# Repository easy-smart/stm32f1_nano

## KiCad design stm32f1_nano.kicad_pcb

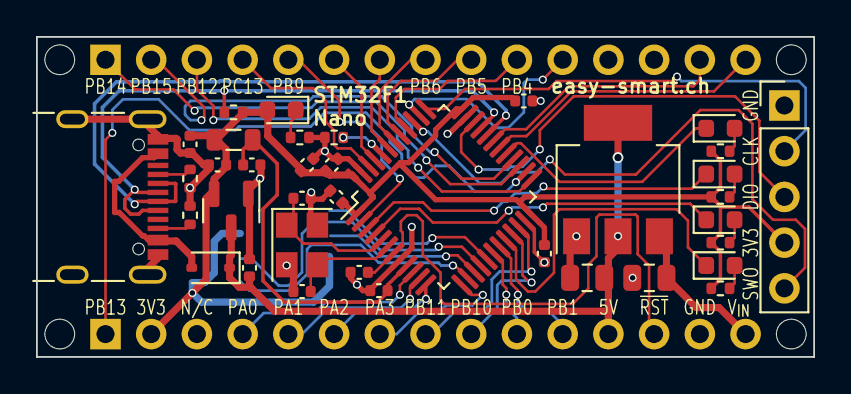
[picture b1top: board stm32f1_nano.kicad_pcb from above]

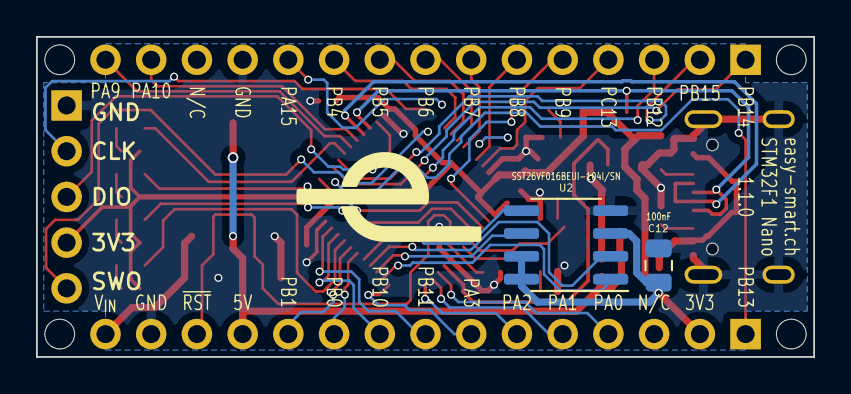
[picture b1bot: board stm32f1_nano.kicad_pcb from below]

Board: 2 copper layers, 43.2 x 17.8 mm, 45 parts (4 on the bottom side), 52 nets.

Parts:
C1, C6: 10n 50V; C_0402_1005Metric
C2, C3, C4, C5, C9: 100n 16V; C_0402_1005Metric
C7, C8, C17, C18: 1u 25V; C_0402_1005Metric
C10, C19: 20p 50V; C_0402_1005Metric
C12: 100nF; C_0805_2012Metric
C15, C16: 22u 25V; C_0805_2012Metric
D1: LED green; LED_0603_1608Metric
D2: LED yellow; LED_0603_1608Metric
D3: LED red; LED_0603_1608Metric
D4: LED blue; LED_0603_1608Metric
D8: PWR LED (grn); LED_0603_1608Metric
D9: 1N5819WS; D_SOD-323
J1: Analog; PinHeader_1x15_P2.54mm_Vertical
J2: Digital; PinHeader_1x15_P2.54mm_Vertical
J3: TYPE-C-31-M-12; SHOU HAN TYPE-C 16PIN 2MD(073)
J5: DEBUG; PinHeader_1x05_P2.54mm_Vertical
L1: 600Ω@100MHz; L_0805_2012Metric
MH1, MH2, MH3, MH4: MountingHole_65mil
R1, R11: 200; R_0402_1005Metric
R2, R3: 330; R_0402_1005Metric
R4: 150; R_0402_1005Metric
R5: 10k; R_0402_1005Metric
R6, R7: 5k1; R_0402_1005Metric
R8: 1k5; R_0402_1005Metric
U1: STM32F103C8T6; LQFP-48_7x7mm_P0.5mm
U2: SST26VF016BEUI-104I/SN; SOIC-8_3.9x4.9mm_P1.27mm
U4: XC6206P332MR; SOT-23
U5: AMS1117-5.0; SOT-223-3_TabPin2
Y1: X322516MLB4SI; Crystal_SMD_3225-4Pin_3.2x2.5mm

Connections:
+3.3V: C1.1, C2.1, C3.1, C4.1, C5.1, C8.1, C12.2, C18.1, D8.2 (A), J1.2, J5.4, L1.2, R2.2, R3.2, R4.2, R8.1, R11.2, U1.1 (VBAT), U1.24 (VDD), U1.36 (VDD), U1.48 (VDD), U2.3 (~WP), U2.7 (~HOLD), U2.8 (VDD), U4.2 (VO)
+3.3VA: C6.1, C7.1, L1.1, U1.9 (VDDA)
+5V: C16.1, C17.1, D9.1 (K), J1.12, U4.3 (VI), U5.2 (VO)
+12V: C15.1, J1.15, U5.3 (VI)
/BOOT0: R5.1, U1.44 (BOOT0)
/HSE_IN: C19.2, U1.5 (PD0), Y1.1
/HSE_OUT: C10.2, U1.6 (PD1), Y1.3
/LED1_GRN: D1.1 (K), U1.4 (PC15)
/LED2_ORG: D2.1 (K), U1.3 (PC14)
/LED3_RED: D3.1 (K), U1.29 (PA8)
/LED4_BLU: D4.1 (K), U1.20 (PB2)
/PA0: J1.4, U1.10 (PA0)
/PA1: J1.5, U1.11 (PA1)
/PA2: J1.6, U1.12 (PA2)
/PA3: J1.7, U1.13 (PA3)
/PA9: J2.15, U1.30 (PA9)
/PA10: J2.14, U1.31 (PA10)
/PA15: J2.11, U1.38 (PA15)
/PB0: J1.10, U1.18 (PB0)
/PB1: J1.11, U1.19 (PB1)
/PB4: J2.10, U1.40 (PB4)
/PB5: J2.9, U1.41 (PB5)
/PB6: J2.8, U1.42 (PB6)
/PB7: J2.7, U1.43 (PB7)
/PB8: J2.6, U1.45 (PB8)
/PB9: J2.4, U1.46 (PB9)
/PB10: J1.9, U1.21 (PB10)
/PB11: J1.8, U1.22 (PB11)
/PB12: J2.3, U1.25 (PB12)
/PB13: J1.1, U1.26 (PB13)
/PB14: J2.1, U1.27 (PB14)
/PB15: J2.2, U1.28 (PB15)
/PC13: J2.5, U1.2 (PC13)
/SPI1_MISO: U1.16 (PA6), U2.2 (SO)
/SPI1_MOSI: U1.17 (PA7), U2.5 (SI)
/SPI1_NSS: U1.14 (PA4), U2.1 (~CE)
/SPI1_SCK: U1.15 (PA5), U2.6 (SCK)
/USB_D+: J3.A6 (D+), J3.B6 (D+), R8.2, U1.33 (PA12)
/USB_D-: J3.A7 (D-), J3.B7 (D-), U1.32 (PA11)
/~RESET: C9.1, J1.13, U1.7 (NRST)
GND: C1.2, C2.2, C3.2, C4.2, C5.2, C6.2, C7.2, C8.2, C9.2, C10.1, C12.1, C15.2, C16.2, C17.2, C18.2, C19.1, J1.14, J2.12, J3.A1 (GND), J3.A12 (GND), J3.B1 (GND), J3.B12 (GND), J3.S1 (SHIELD), J5.1, R1.1, R5.2, R6.1, R7.1, U1.8 (VSSA), U1.23 (VSS), U1.35 (VSS), U1.47 (VSS), U2.4 (VSS), U4.1 (GND), U5.1 (GND), Y1.2, Y1.4
unnamed: D1.2 (A), R11.1
unnamed: D2.2 (A), R2.1
unnamed: D3.2 (A), R3.1
unnamed: D4.2 (A), R4.1
unnamed: D8.1 (K), R1.2
unnamed: J3.A5 (CC1), R6.2
unnamed: J3.B5 (CC2), R7.2
SWCLK: J5.2, U1.37 (PA14)
SWDIO: J5.3, U1.34 (PA13)
SWO: J5.5, U1.39 (PB3)
VBUS: D9.2 (A), J3.A4 (VBUS), J3.A9 (VBUS), J3.B4 (VBUS), J3.B9 (VBUS)

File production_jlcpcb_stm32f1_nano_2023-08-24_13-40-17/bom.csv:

Designator,Footprint,Quantity,Value,LCSC Part #
"C1, C6",0402,2,10n 50V,C15195
"C10, C19",0402,2,20p 50V,C1554
"C15, C16",0805,2,22u 25V,C45783
"C17, C18, C7, C8",0402,4,1u 25V,C52923
"C2, C3, C4, C5, C9",0402,5,100n 16V,C1525
D1,0603,1,LED green,C72043
D2,0603,1,LED yellow,C72038
D3,0603,1,LED red,C2286
D4,0603,1,LED blue,C72041
D8,0603,1,LED red (PWR),C2286
D9,D_SOD-323,1,1N5819WS,C191023
J3,USB_C_Receptacle_HRO_TYPE-C-31-M-12,1,TYPE-C-31-M-12,C165948
L1,0805,1,600Ω@100MHz,C1017
"R1, R2, R3",0402,3,300,C25102
"R11, R4",0402,2,75,C25133
R5,0402,1,10k,C25744
"R6, R7",0402,2,5k1,C25905
R8,0402,1,1k5,C25867
U1,LQFP-48_7x7mm_P0.5mm,1,STM32F103C8T6,C8734
U4,SOT-23-3,1,XC6206P332MR,C5446
U5,SOT-223-3_TabPin2,1,AMS1117-5.0,DNP
Y1,Crystal_SMD_3225-4Pin_3.2x2.5mm,1,X322516MLB4SI,C13738

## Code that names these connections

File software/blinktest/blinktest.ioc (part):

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Mcu.Name=STM32F103C(8-B)Tx
Mcu.Package=LQFP48
Mcu.UserName=STM32F103C8Tx
PA0-WKUP.GPIOParameters=GPIO_Label
PA0-WKUP.GPIO_Label=A0
PA0-WKUP.Signal=ADCx_IN0
PA1.GPIOParameters=GPIO_Label
PA1.GPIO_Label=A1
PA1.Signal=ADCx_IN1
PA10.GPIOParameters=GPIO_Label
PA10.GPIO_Label=USART1_RX/D0
PA10.Mode=Asynchronous
PA10.Signal=USART1_RX
PA11.Mode=Device
PA11.Signal=USB_DM
PA12.Mode=Device
PA12.Signal=USB_DP
PA13.Mode=Trace_Asynchronous_SW
PA13.Signal=SYS_JTMS-SWDIO
PA14.Mode=Trace_Asynchronous_SW
PA14.Signal=SYS_JTCK-SWCLK
PA15.GPIOParameters=GPIO_Label
PA15.GPIO_Label=D2
PA15.Signal=GPIO_Output
PA2.GPIOParameters=GPIO_Label
PA2.GPIO_Label=A2
PA2.Signal=ADCx_IN2
PA3.GPIOParameters=GPIO_Label
PA3.GPIO_Label=A3
PA3.Signal=ADCx_IN3
PA4.Mode=NSS_Signal_Hard_Output
PA4.Signal=SPI1_NSS
PA5.Mode=Full_Duplex_Master
PA5.Signal=SPI1_SCK
PA6.Mode=Full_Duplex_Master
PA6.Signal=SPI1_MISO
PA7.Mode=Full_Duplex_Master
PA7.Signal=SPI1_MOSI
PA8.GPIOParameters=GPIO_Label
PA8.GPIO_Label=LED3_RED
PA8.Signal=GPIO_Output
PA9.GPIOParameters=GPIO_Label
PA9.GPIO_Label=USART1_TX/D1
PA9.Mode=Asynchronous
PA9.Signal=USART1_TX
PB0.GPIOParameters=GPIO_Label
PB0.GPIO_Label=A6
PB0.Signal=ADCx_IN8
PB1.GPIOParameters=GPIO_Label
PB1.GPIO_Label=A7
PB1.Signal=ADCx_IN9
PB10.GPIOParameters=GPIO_Label
PB10.GPIO_Label=I2C2_SCL/A5
PB10.Mode=I2C
PB10.Signal=I2C2_SCL
PB11.GPIOParameters=GPIO_Label
PB11.GPIO_Label=I2C2_SDA/A4
PB11.Mode=I2C
PB11.Signal=I2C2_SDA
PB12.GPIOParameters=GPIO_Label
PB12.GPIO_Label=SPI2_NSS/D10*
PB12.Mode=NSS_Signal_Hard_Input
PB12.Signal=SPI2_NSS
PB13.GPIOParameters=GPIO_Label
PB13.GPIO_Label=SPI2_SCK/D13
PB13.Mode=Full_Duplex_Master
PB13.Signal=SPI2_SCK
PB14.GPIOParameters=GPIO_Label
PB14.GPIO_Label=SPI2_MISO/D12
PB14.Mode=Full_Duplex_Master
PB14.Signal=SPI2_MISO
PB15.GPIOParameters=GPIO_Label
PB15.GPIO_Label=SPI2_MOSI/D11*
PB15.Mode=Full_Duplex_Master
PB15.Signal=SPI2_MOSI
PB2.GPIOParameters=GPIO_Label
PB2.GPIO_Label=LED4_BLU
PB2.Signal=GPIO_Output
PB3.Mode=Trace_Asynchronous_SW
PB3.Signal=SYS_JTDO-TRACESWO
PB4.GPIOParameters=GPIO_Label
PB4.GPIO_Label=D3*
PB4.Signal=GPIO_Analog
PB5.GPIOParameters=GPIO_Label
PB5.GPIO_Label=D4
PB5.Signal=GPIO_Output
PB6.GPIOParameters=GPIO_Label
PB6.GPIO_Label=D5*
PB6.Signal=GPIO_Analog
PB7.GPIOParameters=GPIO_Label
PB7.GPIO_Label=D6*
PB7.Signal=GPIO_Analog
PB8.GPIOParameters=GPIO_Label
PB8.GPIO_Label=D7
PB8.Signal=GPIO_Output
PB9.GPIOParameters=GPIO_Label
PB9.GPIO_Label=D8
PB9.Signal=GPIO_Output
PC13-TAMPER-RTC.GPIOParameters=GPIO_Label
PC13-TAMPER-RTC.GPIO_Label=D9*
PC13-TAMPER-RTC.Signal=GPIO_Analog
PC14-OSC32_IN.GPIOParameters=GPIO_Label
PC14-OSC32_IN.GPIO_Label=LED2_ORG
PC14-OSC32_IN.Signal=GPIO_Output
PC15-OSC32_OUT.GPIOParameters=GPIO_Label
PC15-OSC32_OUT.GPIO_Label=LED1_GRN
PC15-OSC32_OUT.Signal=GPIO_Output
PD0-OSC_IN.Mode=HSE-External-Oscillator
PD0-OSC_IN.Signal=RCC_OSC_IN
PD1-OSC_OUT.Mode=HSE-External-Oscillator
PD1-OSC_OUT.Signal=RCC_OSC_OUT
RCC.HSEDivPLL=RCC_HSE_PREDIV_DIV2
RCC.HSE_VALUE=16000000
RCC.SYSCLKFreq_VALUE=72000000
RCC.SYSCLKSource=RCC_SYSCLKSOURCE_PLLCLK
board=custom

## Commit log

2023-08-21 First draft
2023-08-22 First draft almost done
2023-08-22 New PS
2023-08-22 Reassigned Pins
2023-08-23 Almost done
2023-08-23 First Version released to production
2023-08-24 Corrected distance drill-to-drill and drill-to-track
2023-08-25 JLCPCB Production Files
2023-08-30 Fotos vom Produkt
2023-08-30 mehr Fotos
2023-08-30 Test Software
2023-09-01 Test for SWO
2023-09-04 add datasheet
2023-09-05 Change path, SWO successful
2023-09-05 Add usbtest
2023-09-05 Unblock SWO
2023-09-05 Add flashtest
2023-09-05 #2 green and red LED are too bright
2023-09-05 #3 Make C12 bigger or move to Front
2023-09-05 Change version
2023-09-05 #1 Make debug pins compatible with BluePill
2023-09-05 #5 Check PWM pins
2023-09-05 #4 Can U5 be moved to Front?
2023-09-06 #6 Check RX/TX
2023-09-20 #11 Use new central library KiCad-Lib
2023-09-20 #10 Change USB connector to SHOU HAN TYPE-C 16PIN 2MD(073) (C2765186)
2023-09-20 #8 Use green power led
2023-09-20 #7 Change W25 for a SST26
2023-09-20 Fix missing 3V3 track
2023-09-20 Add PCB 3D model
2023-09-29 Add picture of stm32f1_nano on nano din rail box
2023-10-01 #12 Add pin description to front
2023-10-03 Release 1.1.0 sent to JLCPCB
2023-10-03 PCB production confirmed
2023-10-12 #13 Implement flasheuitest
2023-10-14 Add product photos
2024-02-23 #2 Add github actions
2024-05-03 Add Pinout
